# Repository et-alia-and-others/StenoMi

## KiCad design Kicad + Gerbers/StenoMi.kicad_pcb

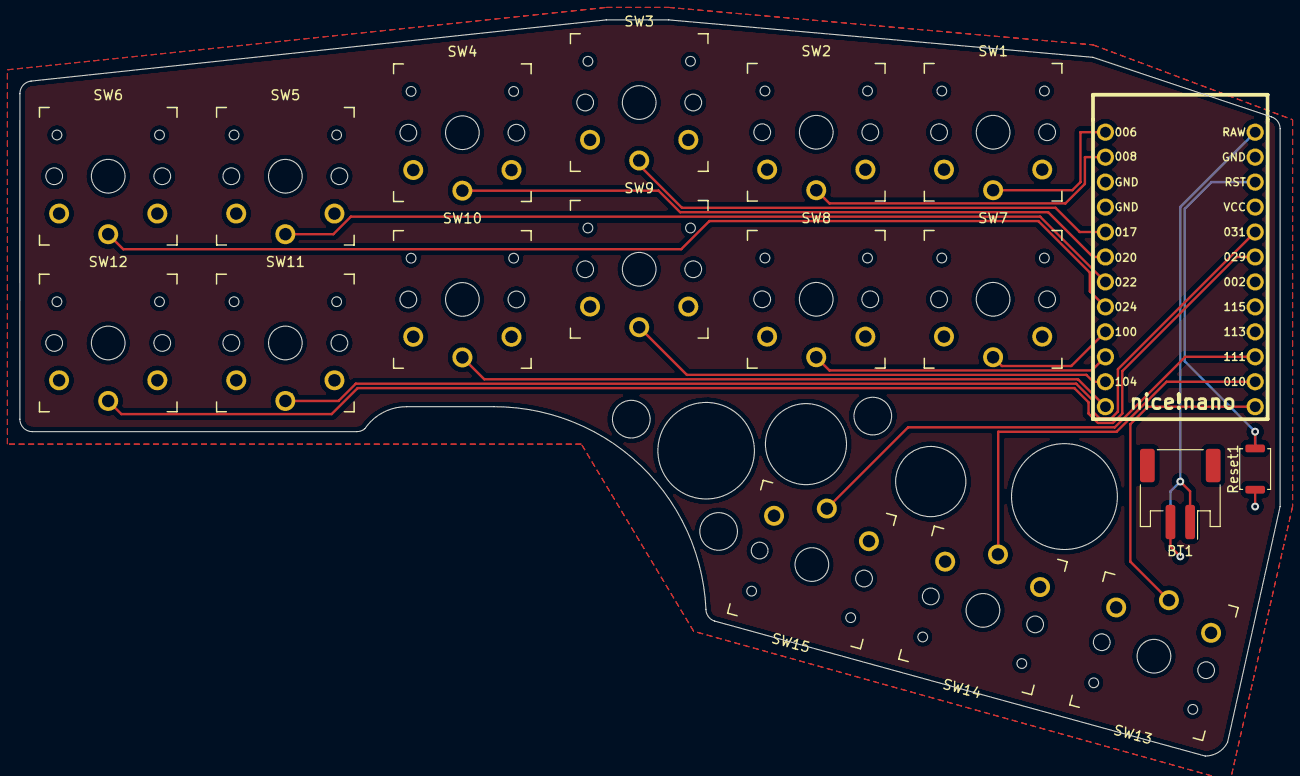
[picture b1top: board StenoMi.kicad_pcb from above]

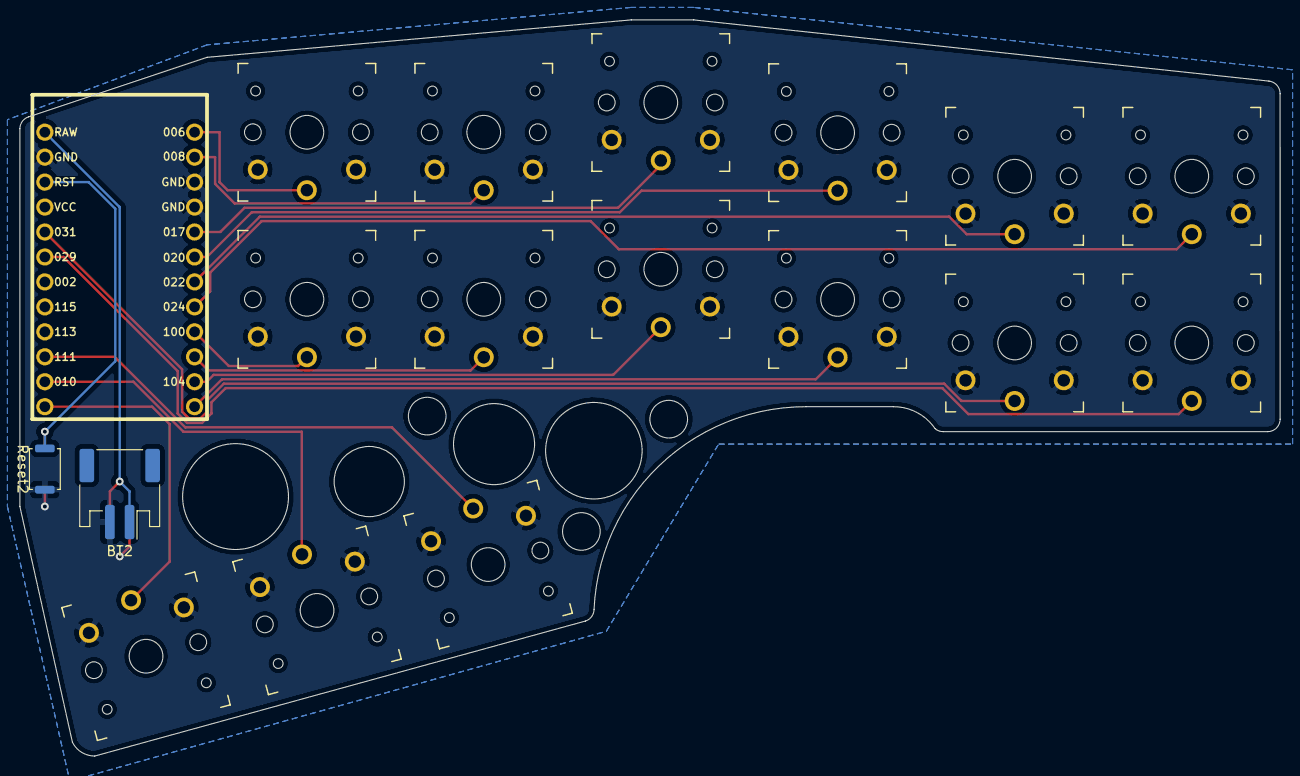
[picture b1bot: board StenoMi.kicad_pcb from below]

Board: 2 copper layers, 128.3 x 74.9 mm, 20 parts (2 on the bottom side), 18 nets.

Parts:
BT1, BT2: Battery; JST_PH_S2B-PH-SM4-TB_1x02-1MP_P2.00mm_Horizontal
Reset1, Reset2: KEYSW; SW_Push_SPST_NO_Alps_SKRK
SW1, SW2, SW3, SW4, SW5, SW6, SW7, SW8, SW9, SW10, SW11, SW12, SW13, SW14, SW15: SW_PUSH; SW_PG1350_reversible
U1: nice_nano

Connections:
Switch1: SW1.1, U1.1
Switch2: SW2.1, U1.2
Switch3: SW3.1, U1.5
Switch4: SW4.1, U1.6
Switch5: SW5.1, U1.7
Switch6: SW6.1, U1.8
Switch7: SW7.1, U1.9
Switch8: SW8.1, U1.10
Switch9: SW9.1, U1.11
Switch10: SW10.1, U1.12
Switch11: SW11.1, U1.20
Switch12: SW12.1, U1.19
Switch13: SW13.1, U1.13
Switch14: SW14.1, U1.14
Switch15: SW15.1, U1.15
gnd: BT1.2, BT2.2, Reset1.1, Reset2.1, SW1.2, SW2.2, SW3.2, SW4.2, SW5.2, SW6.2, SW7.2, SW8.2, SW9.2, SW10.2, SW11.2, SW12.2, SW13.2, SW14.2, SW15.2, U1.3, U1.4, U1.23
raw: BT1.1, BT2.1, U1.24
reset: Reset1.2, Reset2.2, U1.22
